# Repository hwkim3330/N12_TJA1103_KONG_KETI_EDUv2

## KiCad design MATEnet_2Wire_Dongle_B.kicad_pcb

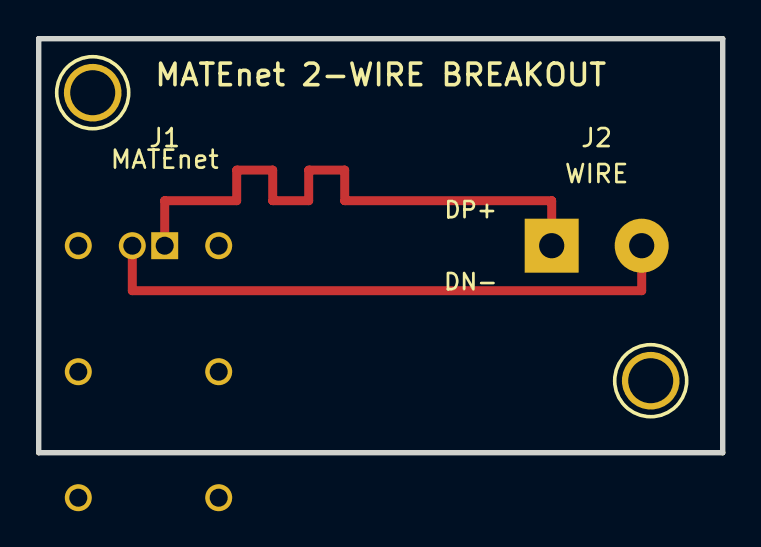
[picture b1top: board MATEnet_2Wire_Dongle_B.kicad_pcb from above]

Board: 2 copper layers, 38.0 x 23.0 mm, 4 parts (0 on the bottom side), 2 nets.

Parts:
H1, H2: MountingHole_2.5mm
J1: 9-2304372-9 MATEnet; 923043729
J2: 2-Pin Wire Clamp; TerminalBlock_WAGO_236-402_1x02_P5.00mm_45Degree

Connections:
MATENET_DN-: J1.2, J2.2
MATENET_DP+: J1.1, J2.1

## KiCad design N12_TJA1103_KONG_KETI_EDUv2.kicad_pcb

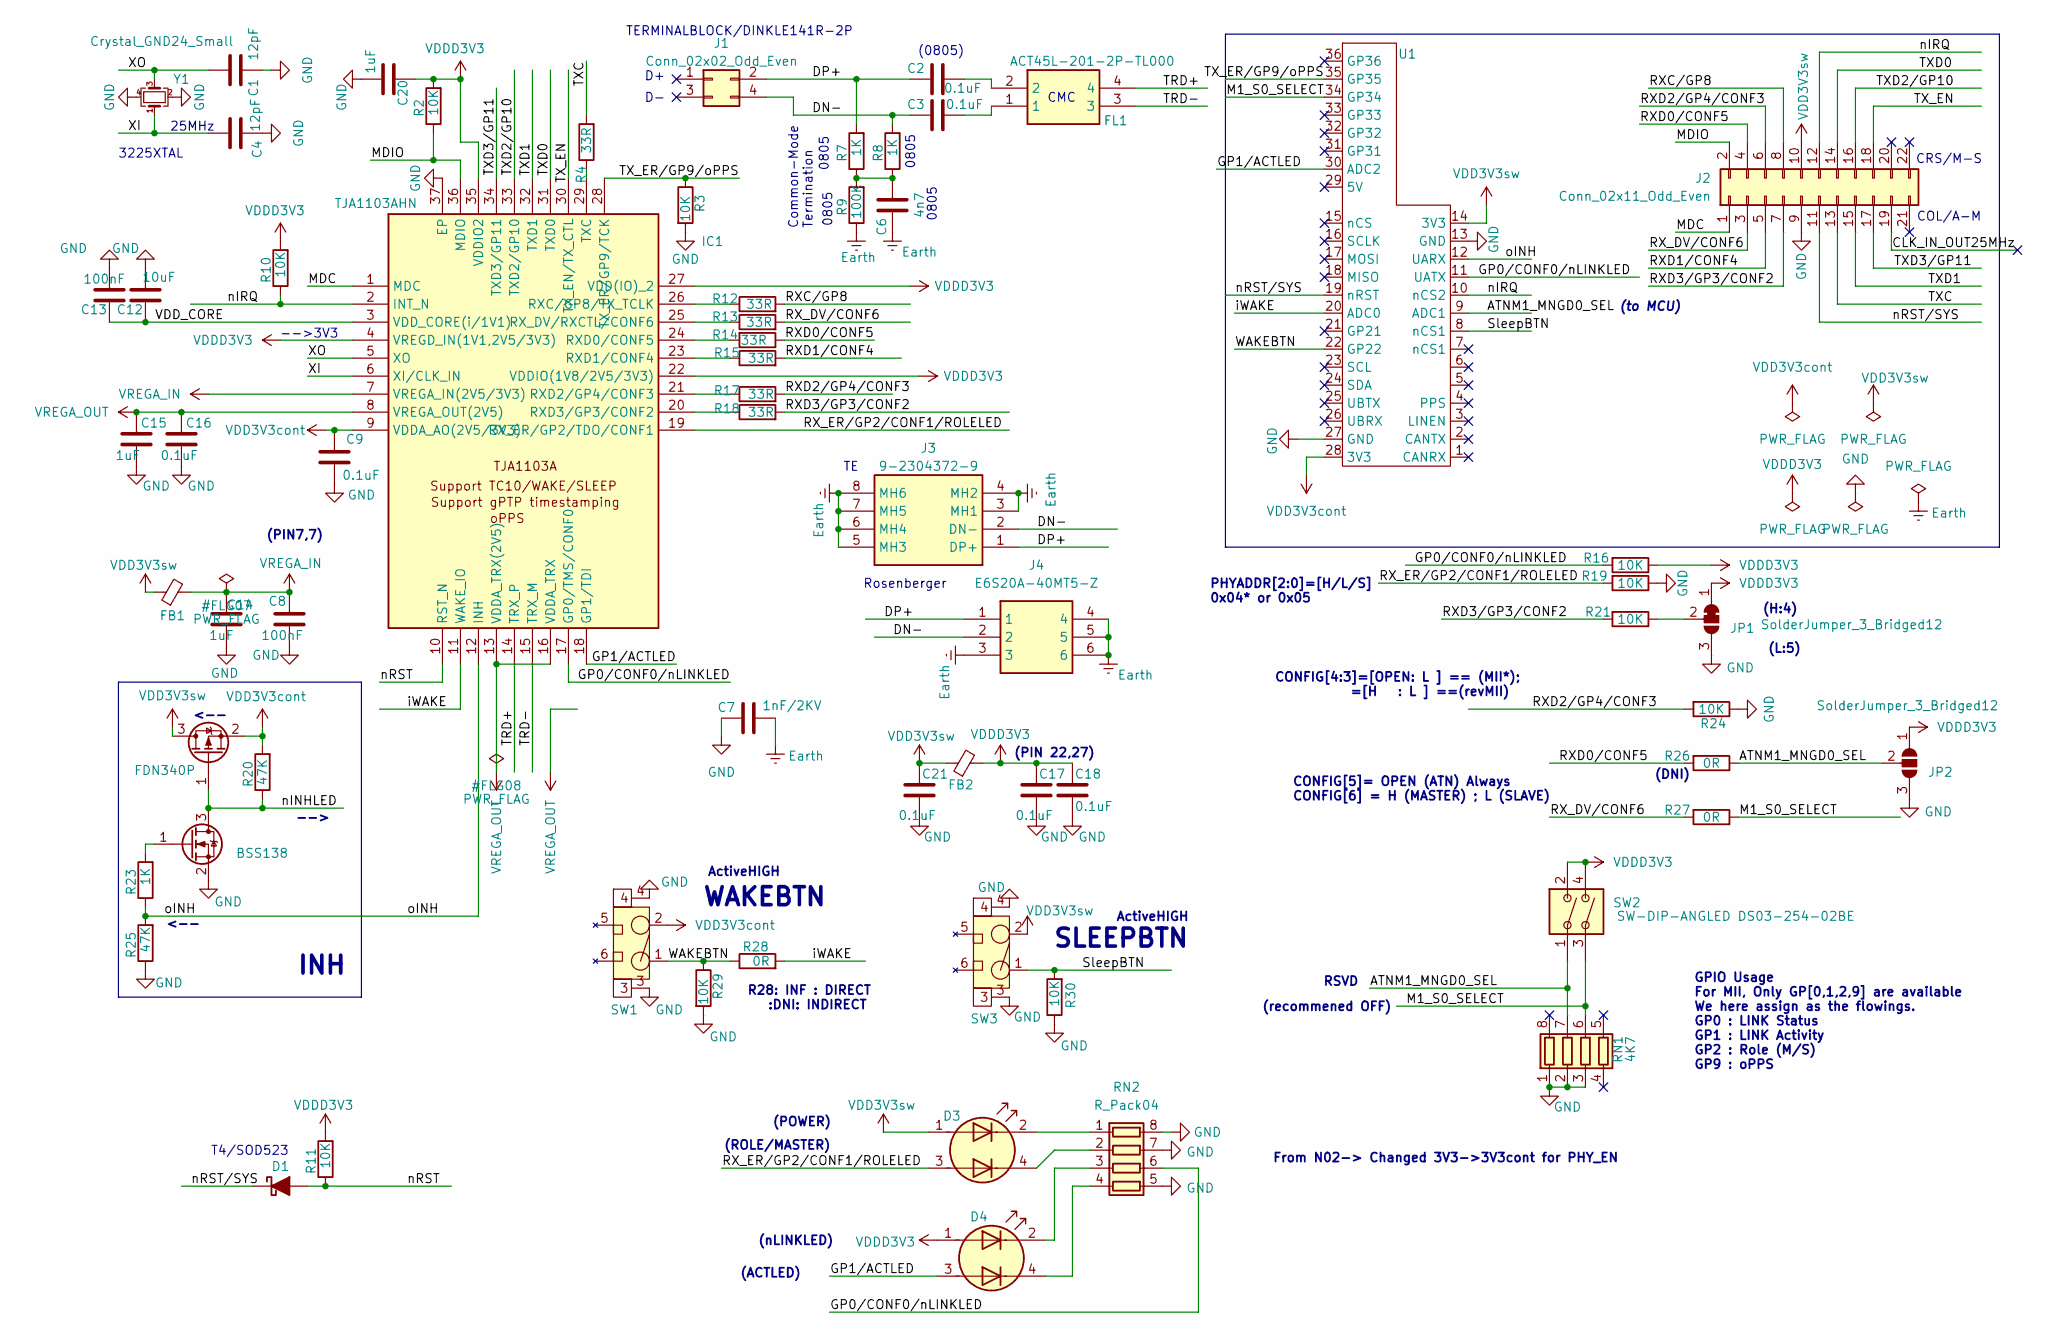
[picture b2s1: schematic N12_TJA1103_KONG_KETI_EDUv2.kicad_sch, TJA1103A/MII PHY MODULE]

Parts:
C1, C4: 12pF; C_0603_1608Metric
C2, C3: 0.1uF; C_0805_2012Metric
C6: 4n7; C_0805_2012Metric
C7: 1nF/2KV; C_1206_3216Metric
C8, C13: 100nF; C_0603_1608Metric
C9, C16, C17, C18, C21: 0.1uF; C_0603_1608Metric
C12: 10uF; C_0603_1608Metric
C14, C15, C20: 1uF; C_0603_1608Metric
D1: D_Schottky_Filled; D_SOD-523
D3, D4: LED_Dual_AKAK; LED_DUAL_SUNGMIN
FB1, FB2: FerriteBead_Small; R_0603_1608Metric
FL1: ACT45L-201-2P-TL000; ACT45L_1; Manufacturer_Part_Number ACT45L-201-2P-TL000; Mouser Part Number 810-ACT45L2012PTL000
IC1: TJA1103AHN; QFN50P600X600X100-37N-D; Manufacturer_Part_Number TJA1101AHN/0Z; Mouser Part Number 771-TJA1101AHN/0Z
J1: Conn_02x02_Odd_Even; TERMINALBLOCK_DINKLE_141R-2P
J2: Conn_02x11_Odd_Even; PinHeader_2x11_P2.54mm_Vertical
J3: 9-2304372-9; 923043729_TE; Manufacturer_Part_Number 9-2304372-9; Mouser Part Number 571-9-2304372-9
J4: E6S20A-40MT5-Z; E6S20A40MT5Z; Manufacturer_Part_Number E6S20A-40MT5-Z; Mouser Part Number 476-E6S20A-40MT5-Z
JP1: SolderJumper_3_Bridged12; SolderJumper-3_P1.3mm_Bridged12_RoundedPad1.0x1.5mm
JP2: SolderJumper_3_Bridged12; SolderJumper-3_P1.3mm_Open_RoundedPad1.0x1.5mm
Q1: FDN340P; SOT-23
Q2: BSS138; SOT-23
R2, R3, R10, R11, R16, R19, R21, R24, R29, R30: 10K; R_0603_1608Metric
R4, R12, R13, R14, R15, R17, R18: 33R; R_0402_1005Metric
R7, R8: 1K; R_0805_2012Metric
R9: 100K; R_0805_2012Metric
R20, R25: 47K; R_0603_1608Metric
R23: 1K; R_0603_1608Metric
R26, R27, R28: 0R; R_0603_1608Metric
RN1: 4K7; R_ARRAY4_0603
RN2: R_Pack04; R_ARRAY4_0603
SW1, SW3: SW_TACT_2X4MM_YOON
SW2: SW-DIP-ANGLED DS03-254-02BE; SW_DIP_ANGLED_DS0325402BE; Manufacturer_Part_Number DS03-254-02BE; Mouser Part Number 490-DS03-254-02BE
U1: CONN_14X2+8_KONG
Y1: Crystal_GND24_Small; Crystal_SMD_3225-4Pin_3.2x2.5mm

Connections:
/ATNM1_MNGD0_SEL: JP2.2 (C), R26.1, RN1.7 (R2.2), SW2.1, U1.9 (ADC1)
/CLK_IN_OUT25MHz: J2.19
/DN-: C3.1, J1.4, J3.2 (DP+), J4.2, R8.2
/DP+: C2.1, J1.2, J3.1 (DN-), J4.1, R7.2
/GP0/CONF0/nLINKLED: IC1.17 (GP0/TMS/CONF0), R16.2, RN2.6 (R3.2), U1.11 (UATX)
/GP1/ACTLED: D4.3 (A2), IC1.18 (GP1/TDI), U1.30 (ADC2)
/M1_S0_SELECT: R27.1, RN1.6 (R3.2), SW2.3, U1.34 (GP34)
/MDC: IC1.1 (MDC), J2.1
/MDIO: IC1.36 (MDIO), J2.2, R2.1
/RXC/GP8: J2.8, R12.2
/RXD0/CONF5: J2.4, R14.1, R26.2
/RXD1/CONF4: J2.5, R15.2
/RXD2/GP4/CONF3: J2.6, R17.2, R24.2
/RXD3/GP3/CONF2: J2.7, R18.2, R21.2
/RX_DV/CONF6: J2.3, R13.2, R27.2
/RX_ER/GP2/CONF1/ROLELED: D3.3 (A2), IC1.19 (RX_ER/GP2/TDO/CONF1), R19.2
/SleepBTN: R30.2, SW3.1, U1.8 (nCS1)
/TRD+: FL1.4, IC1.14 (TRX_P)
/TRD-: FL1.3, IC1.15 (TRX_M)
/TXC: J2.13, R4.2
/TXD0: IC1.31 (TXD0), J2.14
/TXD1: IC1.32 (TXD1), J2.15
/TXD2/GP10: IC1.33 (TXD2/GP10), J2.16
/TXD3/GP11: IC1.34 (TXD3/GP11), J2.17
/TX_EN: IC1.30 (TX_EN/TX_CTL), J2.18
/TX_ER/GP9/oPPS: IC1.28 (TX_ER/GP9/TCK), R3.1, U1.35 (GP35)
/VDD_CORE: C12.1, C13.1, IC1.3 (VDD_CORE(i/1V1))
/WAKEBTN: R28.1, R29.1, SW1.1, U1.22 (GP22)
/XI: C4.1, IC1.6 (XI/CLK_IN), Y1.1
/XO: C1.1, IC1.5 (XO), Y1.3
/iWAKE: IC1.11 (WAKE_IO), R28.2, U1.20 (ADC0)
/nINHLED: Q1.1 (G), Q2.3 (D), R20.1
/nIRQ: IC1.2 (INT_N), J2.12, R10.1, U1.10 (nCS2)
/nRST: D1.2 (A), IC1.10 (RST_N), R11.1
/nRST/SYS: D1.1 (K), J2.11, U1.19 (nRST)
/oINH: IC1.12 (INH), R23.1, R25.2, U1.12 (UARX)
Earth: C6.1, C7.2, J3.3 (MH1), J3.4 (MH2), J3.5 (MH3), J3.6 (MH4), J3.7 (MH5), J3.8 (MH6), J4.3, J4.4, J4.5, J4.6, R9.1
GND: C1.2, C4.2, C7.1, C8.2, C9.2, C12.2, C13.2, C14.2, C15.2, C16.2, C17.2, C18.2, C20.2, C21.2, IC1.37 (EP), J2.9, JP1.3 (B), JP2.3 (B), Q2.2 (S), R3.2, R19.1, R24.1, R25.1, R29.2, R30.1, RN1.1 (R1.1), RN1.2 (R2.1), RN1.3 (R3.1), RN2.5 (R4.2), RN2.7 (R2.2), RN2.8 (R1.2), SW1.3, SW1.4, SW3.3, SW3.4, U1.13 (GND), U1.27 (GND), Y1.2, Y1.4
unnamed: C2.2, FL1.2
unnamed: C3.2, FL1.1
unnamed: C6.2, R7.1, R8.1, R9.2
unnamed: D3.2 (K1), RN2.1 (R1.1)
unnamed: D3.4 (K2), RN2.2 (R2.1)
unnamed: D4.2 (K1), RN2.3 (R3.1)
unnamed: D4.4 (K2), RN2.4 (R4.1)
unnamed: IC1.26 (RXC/GP8/TX_TCLK), R12.1
unnamed: IC1.24 (RXD0/CONF5), R14.2
unnamed: IC1.23 (RXD1/CONF4), R15.1
unnamed: IC1.21 (RXD2/GP4/CONF3), R17.1
unnamed: IC1.20 (RXD3/GP3/CONF2), R18.1
unnamed: IC1.25 (RX_DV/RXCTL/CONF6), R13.1
unnamed: IC1.29 (TXC), R4.1
unnamed: JP1.2 (C), R21.1
unnamed: Q2.1 (G), R23.2
VDD3V3cont: C9.1, IC1.9 (VDDA_AO(2V5/3V3)), Q1.2 (S), R20.2, SW1.2, U1.28 (3V3)
VDD3V3sw: C21.1, D3.1 (A1), FB1.1, FB2.1, J2.10, Q1.3 (D), SW3.2, U1.14 (3V3)
VDDD3V3: C17.1, C18.1, C20.1, D4.1 (A1), FB2.2, IC1.4 (VREGD_IN(1V1,2V5/3V3)), IC1.22 (VDDIO(1V8/2V5/3V3)), IC1.27 (VDD(IO)_2), IC1.35 (VDDIO2), JP1.1 (A), JP2.1 (A), R2.2, R10.2, R11.2, R16.1, SW2.2, SW2.4
VREGA_IN: C8.1, C14.1, FB1.2, IC1.7 (VREGA_IN(2V5/3V3))
VREGA_OUT: C15.1, C16.1, IC1.8 (VREGA_OUT(2V5)), IC1.13 (VDDA_TRX(2V5)), IC1.16 (VDDA_TRX)

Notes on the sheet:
CONFIG[4:3]=[OPEN: L ] == (MII*); =[H : L ] ==(revMII)
Rosenberger
0805
CRS/M-S
-->
From N02-> Changed 3V3->3V3cont for PHY_EN
-->3V3
3225XTAL
(ROLE/MASTER)
25MHz
PHYADDR[2:0]=[H/L/S] 0x04* or 0x05
ActiveHIGH
(recommened OFF)
TERMINALBLOCK/DINKLE141R-2P
(PIN7,7)
<--
(to MCU)
SLEEPBTN
Common-Mode Termination
T4/SOD523
INH
CONFIG[5]= OPEN (ATN) Always CONFIG[6] = H (MASTER) ; L (SLAVE)
GPIO Usage For MII, Only GP[0,1,2,9] are available We here assign as the flowings. GP0 : LINK Status GP1 : LINK Activity GP2 : Role (M/S) GP9 : oPPS
(L:5)
(0805)
RSVD
0805
(DNI)
(H:4)
COL/A-M
CMC
WAKEBTN
(nLINKLED)
(ACTLED)
(POWER)
R28: INF : DIRECT :DNI: INDIRECT
(PIN 22,27)

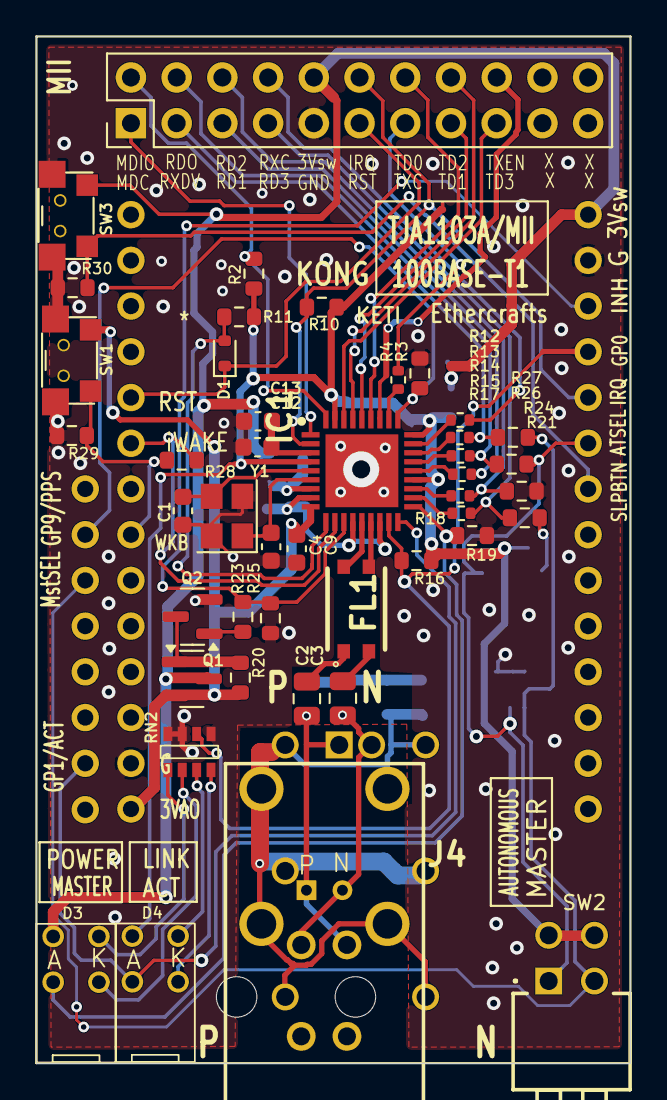
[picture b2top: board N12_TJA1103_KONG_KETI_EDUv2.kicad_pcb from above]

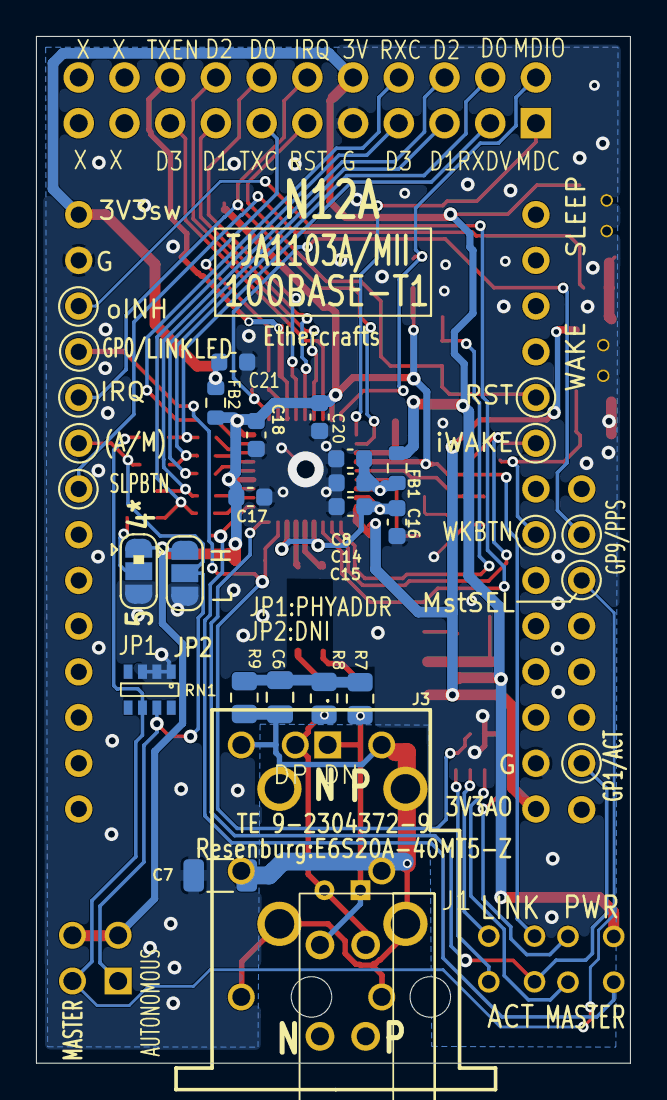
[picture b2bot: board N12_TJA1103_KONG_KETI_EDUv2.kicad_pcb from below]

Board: 2 copper layers, 33.0 x 57.0 mm, 65 parts (20 on the bottom side), 58 nets.

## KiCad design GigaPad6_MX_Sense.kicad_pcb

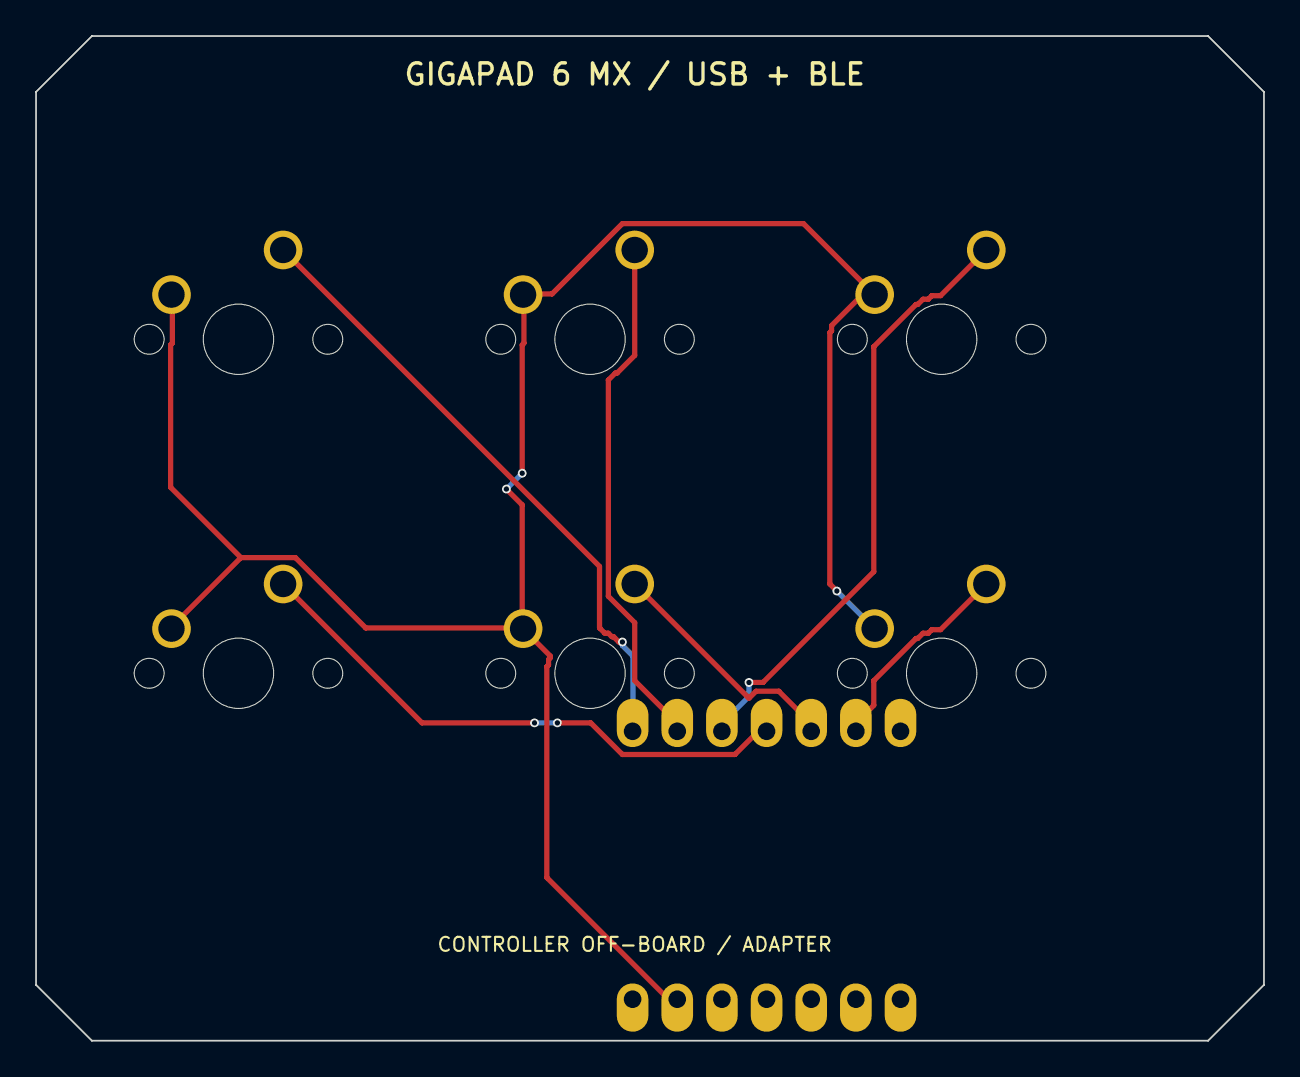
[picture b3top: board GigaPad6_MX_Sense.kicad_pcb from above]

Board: 2 copper layers, 69.8 x 57.2 mm, 7 parts (1 on the bottom side), 7 nets.

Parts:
SW1, SW2, SW3, SW4, SW5, SW6: SW_Push; SW_Cherry_MX_1.00u_PCB
U1: CONTROLLER_HOST_2x07

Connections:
GND: SW1.2, SW2.2, SW3.2, SW4.2, SW5.2, SW6.2, U1.13 (GND)
SW_1: SW1.1, U1.1 (PA02_A0_D0)
SW_2: SW2.1, U1.2 (PA4_A1_D1)
SW_3: SW3.1, U1.3 (PA10_A2_D2)
SW_4: SW4.1, U1.4 (PA11_A3_D3)
SW_5: SW5.1, U1.5 (PA8_A4_D4_SDA)
SW_6: SW6.1, U1.6 (PA9_A5_D5_SCL)

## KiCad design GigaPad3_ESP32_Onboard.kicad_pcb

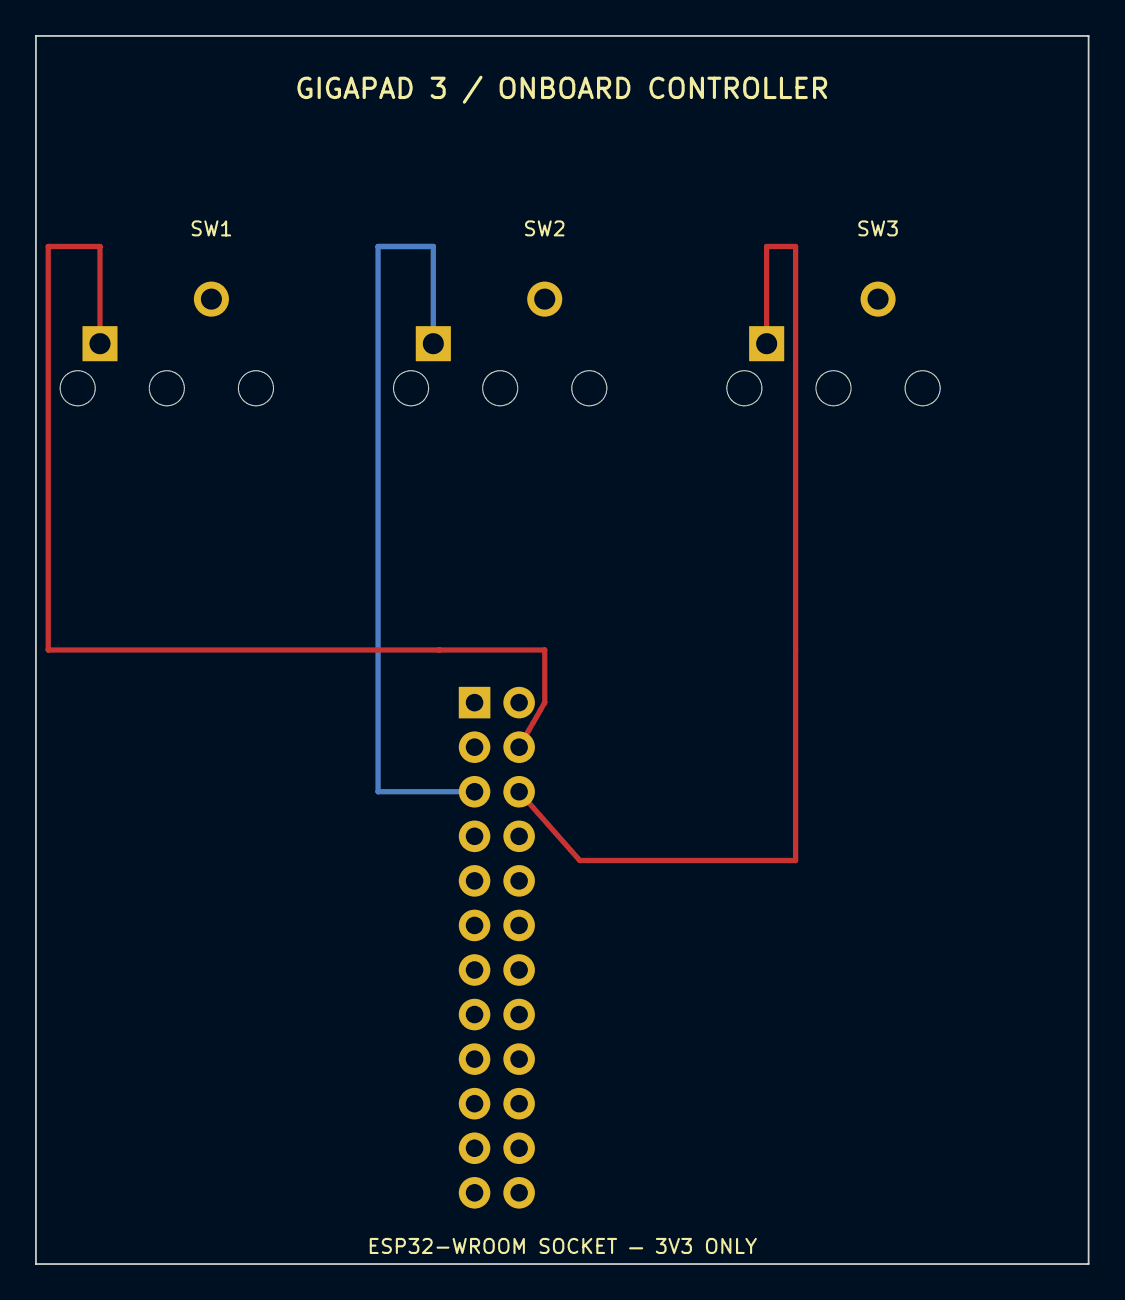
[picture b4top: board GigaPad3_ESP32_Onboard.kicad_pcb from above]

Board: 2 copper layers, 60.0 x 70.0 mm, 4 parts (1 on the bottom side), 4 nets.

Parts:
SW1, SW2, SW3: Cherry_MX_1u
U1: ESP32-WROOM 3V3; ESP32_WROOM_CARRIER_2x12_P2.54mm

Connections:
GND: SW1.2, SW2.2, SW3.2, U1.3, U1.9, U1.10
SW_1: SW1.1, U1.4
SW_2: SW2.1, U1.5
SW_3: SW3.1, U1.6
